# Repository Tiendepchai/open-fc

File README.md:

# open-fc (OPEN-FC MINIMAL v1.0 — Carrier PCB Rev K)

> **Status:** `HARDWARE DESIGN (REV K) & M0 VERIFICATION — BENCH ONLY` (Not flight-certified).

Custom minimal flight-controller carrier & companion stack built around a `WeAct STM32F405RGT6` running `ArduCopter / ChibiOS` (`OPENFCF405`) as the single flight-critical authority, paired with `ESP32 DevKit` (MAVLink2 Wi-Fi telemetry bridge) and `ESP32-CAM` (`OV2640` vision precision landing).

## Baseline Summary (Rev K — 100% THT)

- **Carrier PCB (`design`):** `60 × 68 mm` (`Rev K.1`, ADR-003), 2-layer FR4, 4× M3 mounting holes (`45 × 45 mm`), 100% THT (`23` discrete + `12` headers/sockets = `35` electrical parts + `4` M3 holes). Open-sky `U1` (`33.22×41.60 mm`), `U2` (`25.10×14.88 mm`), `U3` (`15.38×11.50 mm`); low-profile discretes (`≤ 5.5 mm`) nested under `U1`.
- **VBAT Sense (`design`):** Passive current-limited divider `220 kΩ (1%) / 18 kΩ (1%)` + `4.7 kΩ` series + `100 nF` into `PA0` (`TMUX1511PW` removed). `JP_C` (`PC0` current sense) stays **OPEN** by default.
- **Power Option 1 — Pixhawk Style (`confirmed`):** External UBEC `5V/3A` off ESC `BAT+ / BAT-` into `J_PWR (JST-XH 2P)`, star-routed into `+5V_COMP` (`J_WIFI`, `J_CAM`, `C1/C2 470 µF`) and `+5V_FC` via Schottky `D1 1N5822` (`U1`, `J_GPS`, `J_RC`, `C6 100 nF`).
- **Sensors & Peripherals (`measured` / `design`):** `MPU6500` + `BMP280` on `SPI1` (internal `~9 kΩ` CS pull-ups measured; external CS pull-ups removed), `BN-880` on `USART6` + `I2C2` (`18 kΩ` measured on module; PCB adds `R9/R10 4.7 kΩ` to `+3V3`), `MC7RE` SBUS on `UART4` via external inverted SBUS carrier PCB + `R12 (4.7 kΩ)` series protection (ADR-003).
- **Connectors (`confirmed`):** Standardized vertical THT `JST-XH 2.50 mm` (`2P, 3P, 4P×2, 6P, 8P`), `Pin 1 = +V`, `Pin 2 = GND` on all power-carrying ports.

## Roadmap Status

| Milestone | Scope | Status |
|---|---|---|
| **M0 — Hardware Verification** | Cold checks done (`PA9`, `NCS/CSB`, `BN-880 I2C`, pad orders); WeAct F405 V11 `8 MHz` HSE + `2×15` pinmap `1..30` + `ΔX = 27.94 mm` locked from vendor docs. Pending: 1:1 A4 paper fit check, `JST-XH` cable wiring polarity, `MC7RE` SBUS waveform, UBEC `5V/3A` dual-ESP32 load test. | **In Progress** |
| **M1 — PCB Rev K & FC Port** | **FW (`PASS`):** `OPENFCF405` (`Copter-4.6.3`, `HSE 8 MHz`) builds at `735,816 / 983,040 B` (`247 KB` headroom) with `SHARED_DMA_MASK=0` (`TIM4_UP` DMAR dedicated). **Schematic (`PASS`):** 4-sheet KiCad 10 Rev K.1 (`U1_P1/U1_P2` `verified_from_vendor_doc`, external SBUS carrier + `R12 4.7 kΩ`, `0` ERC violations, BOM sync `PASS` `23` discrete + `12` headers/connectors). **PCB (`PASS` / `design`):** `60 × 68 mm` 2-layer layout (`B.Cu` GND plane, `308` tracks, `67` vias, `45 × 45 mm` M3, `25.40 mm` WeAct inner-to-inner, open-sky `MPU6500`/`BMP280`/`WeAct` with 1:1 `F.Fab` outlines, low-profile discretes under `U1`), **`0` DRC errors/warnings/unconnected/parity**; **1:1 A4 PDF** at `hardware/fabrication/open-fc-carrier-rev-k-1to1-A4.pdf` (physical fit check pending). | **In Progress (FW + Sch + PCB DRC=0 PASS; Fit Check Pending)** |
| **M2 — Carrier Bring-up & Gateway** | Staged PCB solder (`PA0` check pre-MCU), ArduCopter bench bring-up (props off), `esp32-wifi` MAVLink2 UDP↔UART1 bridge. | Planned |
| **M3 — Vision Pipeline** | `OV2640` calibration, `esp32-cam` marker detection → MAVLink2 `LANDING_TARGET`, FPS/latency benchmark. | Planned |
| **M4 — SITL & Bench Integration** | ArduCopter SITL + vision replay; F450 prop-off bench fault-injection tests. | Planned |
| **M5 — Flight Release** | IMU damping, BMP280 wind foam, measured `BATT_VOLT_MULT`, `docs/safety-case.md` approval. | **BLOCKED** |

## Repository Map

- `AGENTS.md` — mandatory engineering guardrails and safety rules.
- `docs/` — master baseline (`OPEN_FC_MINIMAL_v1.0.md`), verified pinmap, Rev K BOM, ADRs, verification logs, safety case.
- `hardware/` — KiCad Rev K project, reference schematics, fabrication outputs, mechanical mounts.
- `firmware/` — pinned `ardupilot/` submodule, custom `board-openfcf405/`, `esp32-wifi/`, `esp32-cam/`.
- `sim/` — SITL launch configs, vision replay datasets, fault-injection scenarios.
- `scripts/` — FC build + 1 MB Flash check (`build-fc.sh`), ChibiOS DMA analyzer (`check-dma.py`), BOM sync check (`check-bom-sync.py`).
- `reports/` — dated build logs, ERC/DRC reports, bench verification outputs.

## Quick Commands (M1–M4 Software Verification)

```bash
# 1. Verify BOM CSV consistency (and cross-check KiCad export when available)
python3 scripts/check-bom-sync.py

# 2. Build OPENFCF405 bootloader + ArduCopter (verifies < 1 MB Flash, TIM4 DMA, 11 ELF safety symbols)
./scripts/build-fc.sh

# 3. Verify companion C11 modules (esp32-wifi, esp32-cam), vision replay, and M4 fault-injection suite
./scripts/test-companions.sh

# 4. Run KiCad 10 ERC=0, DRC=0 + schematic parity, 1:1 A4 PDF export, and BOM sync (once PCB exists)
./scripts/verify-kicad.sh
```

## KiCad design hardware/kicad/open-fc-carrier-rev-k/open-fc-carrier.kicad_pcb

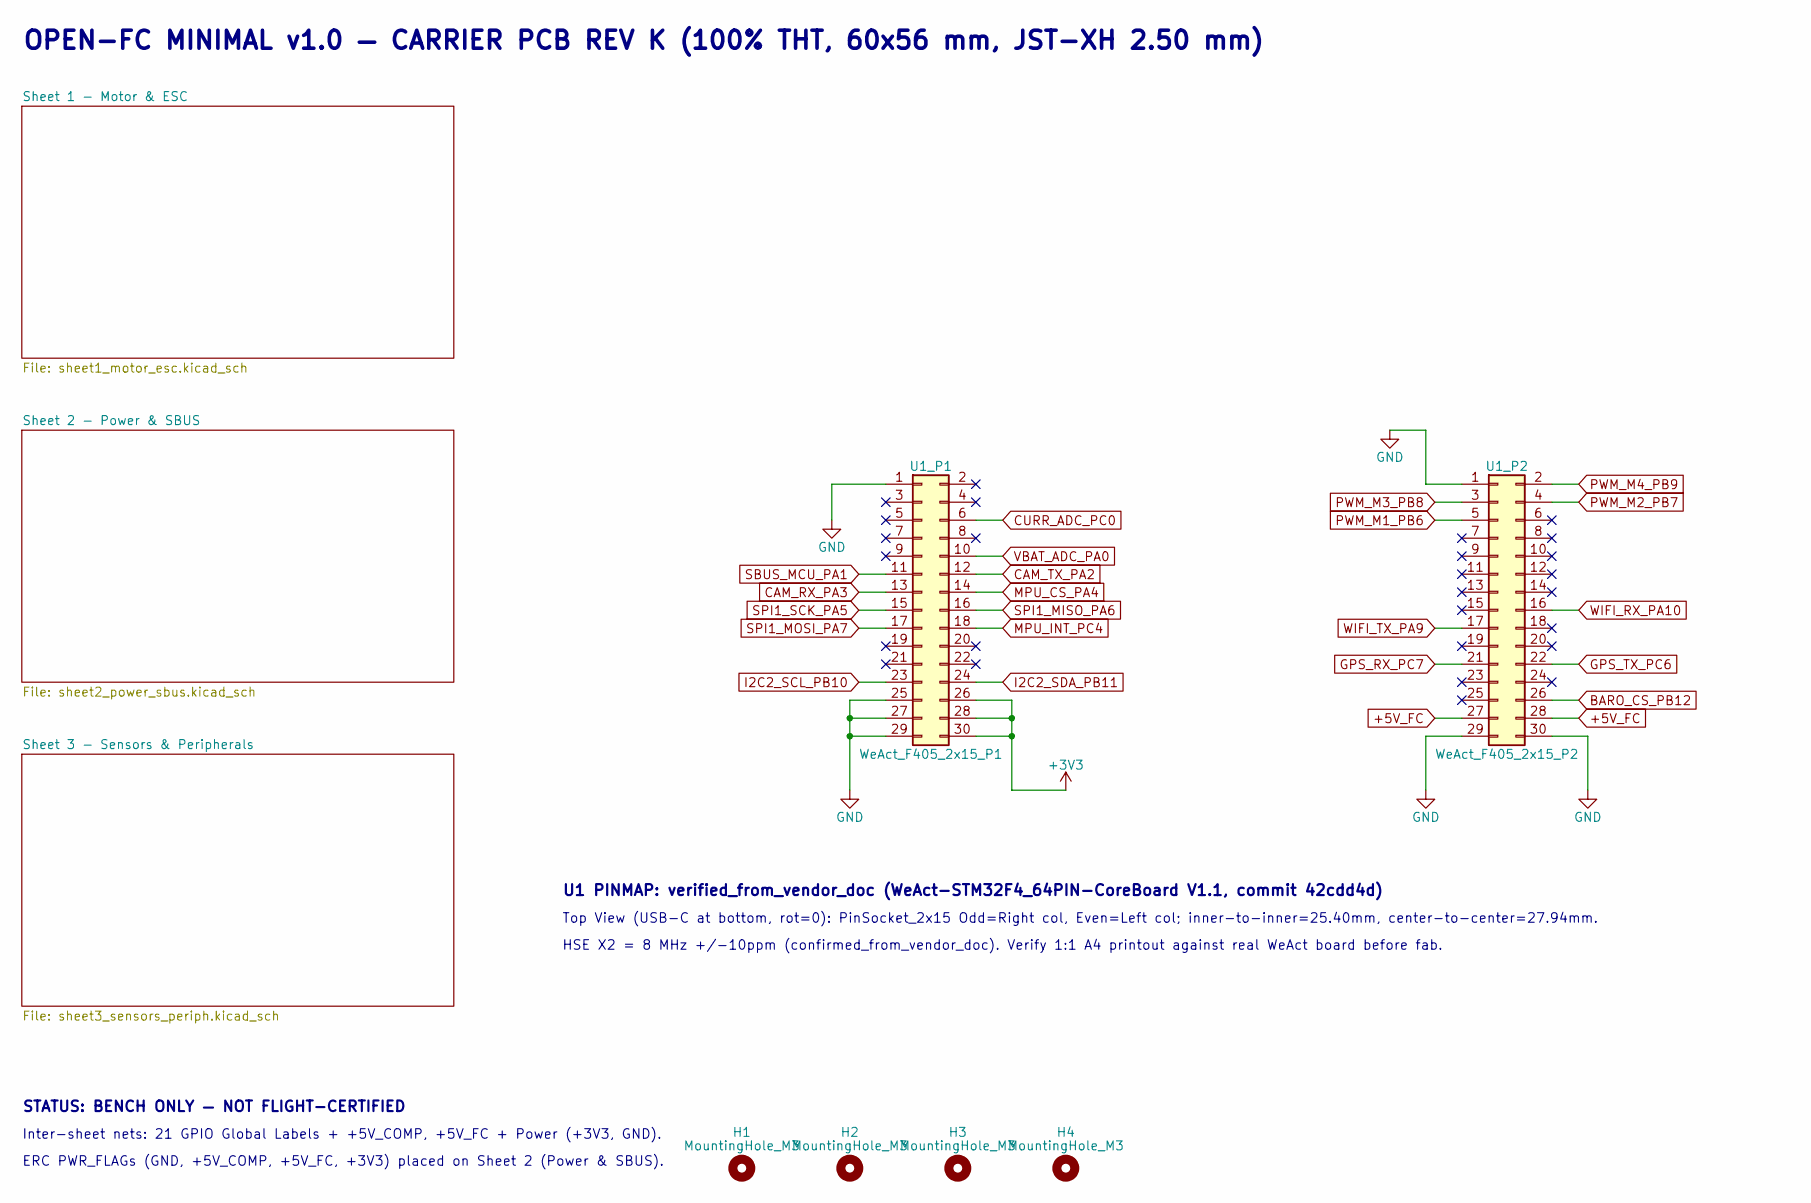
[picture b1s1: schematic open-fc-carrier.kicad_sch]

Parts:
H1, H2, H3, H4: MountingHole_M3; MountingHole_3.2mm_M3
U1_P1: WeAct_F405_2x15_P1; PinSocket_2x15_P2.54mm_Vertical
U1_P2: WeAct_F405_2x15_P2; PinSocket_2x15_P2.54mm_Vertical

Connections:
+3V3: U1_P1.26, U1_P1.28, U1_P1.30; also elsewhere on the board
+5V_FC: U1_P2.27, U1_P2.28; also elsewhere on the board
BARO_CS_PB12: U1_P2.26; also elsewhere on the board
CAM_RX_PA3: U1_P1.13; also elsewhere on the board
CAM_TX_PA2: U1_P1.12; also elsewhere on the board
CURR_ADC_PC0: U1_P1.6; also elsewhere on the board
GND: U1_P1.1, U1_P1.25, U1_P1.27, U1_P1.29, U1_P2.1, U1_P2.29, U1_P2.30; also elsewhere on the board
GPS_RX_PC7: U1_P2.21; also elsewhere on the board
GPS_TX_PC6: U1_P2.22; also elsewhere on the board
I2C2_SCL_PB10: U1_P1.23; also elsewhere on the board
I2C2_SDA_PB11: U1_P1.24; also elsewhere on the board
MPU_CS_PA4: U1_P1.14; also elsewhere on the board
MPU_INT_PC4: U1_P1.18; also elsewhere on the board
PWM_M1_PB6: U1_P2.5; also elsewhere on the board
PWM_M2_PB7: U1_P2.4; also elsewhere on the board
PWM_M3_PB8: U1_P2.3; also elsewhere on the board
PWM_M4_PB9: U1_P2.2; also elsewhere on the board
SBUS_MCU_PA1: U1_P1.11; also elsewhere on the board
SPI1_MISO_PA6: U1_P1.16; also elsewhere on the board
SPI1_MOSI_PA7: U1_P1.17; also elsewhere on the board
SPI1_SCK_PA5: U1_P1.15; also elsewhere on the board
VBAT_ADC_PA0: U1_P1.10; also elsewhere on the board
WIFI_RX_PA10: U1_P2.16; also elsewhere on the board
WIFI_TX_PA9: U1_P2.17; also elsewhere on the board

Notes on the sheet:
OPEN-FC MINIMAL v1.0 — CARRIER PCB REV K (100% THT, 60x56 mm, JST-XH 2.50 mm)
STATUS: BENCH ONLY — NOT FLIGHT-CERTIFIED
Inter-sheet nets: 21 GPIO Global Labels + +5V_COMP, +5V_FC + Power (+3V3, GND).
ERC PWR_FLAGs (GND, +5V_COMP, +5V_FC, +3V3) placed on Sheet 2 (Power & SBUS).
U1 PINMAP: verified_from_vendor_doc (WeAct-STM32F4_64PIN-CoreBoard V1.1, commit 42cdd4d)
Top View (USB-C at bottom, rot=0): PinSocket_2x15 Odd=Right col, Even=Left col; inner-to-inner=25.40mm, center-to-center=27.94mm.
HSE X2 = 8 MHz +/-10ppm (confirmed_from_vendor_doc). Verify 1:1 A4 printout against real WeAct board before fab.

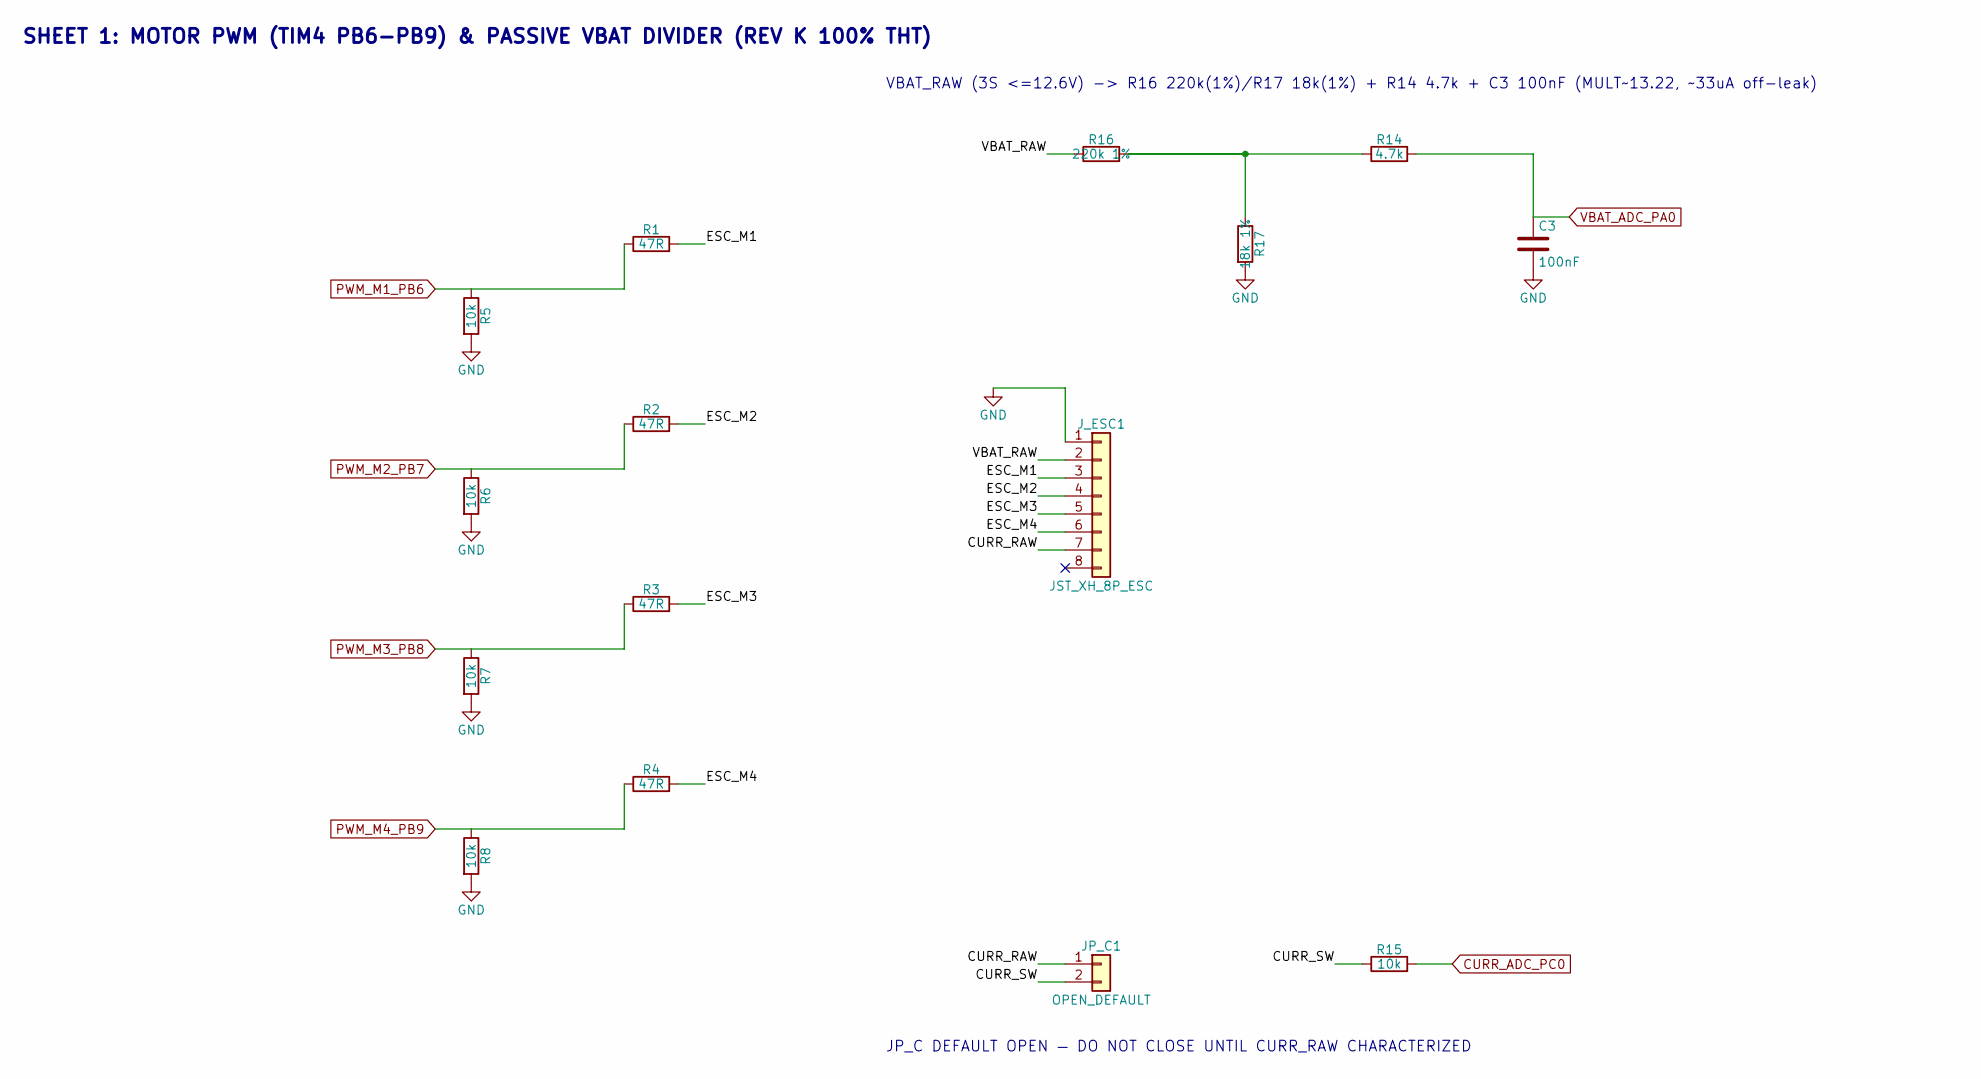
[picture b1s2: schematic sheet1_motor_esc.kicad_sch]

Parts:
C3: 100nF; C_Disc_D5.0mm_W2.5mm_P5.00mm
JP_C1: OPEN_DEFAULT; PinHeader_1x02_P2.54mm_Vertical
J_ESC1: JST_XH_8P_ESC; JST_XH_B8B-XH-A_1x08_P2.50mm_Vertical
R1, R2, R3, R4: 47R; R_Axial_DIN0207_L6.3mm_D2.5mm_P7.62mm_Horizontal
R5, R6, R7, R8, R15: 10k; R_Axial_DIN0207_L6.3mm_D2.5mm_P7.62mm_Horizontal
R14: 4.7k; R_Axial_DIN0207_L6.3mm_D2.5mm_P7.62mm_Horizontal
R16: 220k 1%; R_Axial_DIN0207_L6.3mm_D2.5mm_P7.62mm_Horizontal
R17: 18k 1%; R_Axial_DIN0207_L6.3mm_D2.5mm_P7.62mm_Horizontal

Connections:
/Sheet 1 - Motor & ESC/CURR_RAW: JP_C1.1, J_ESC1.7
/Sheet 1 - Motor & ESC/CURR_SW: JP_C1.2, R15.1
/Sheet 1 - Motor & ESC/ESC_M1: J_ESC1.3, R1.2
/Sheet 1 - Motor & ESC/ESC_M2: J_ESC1.4, R2.2
/Sheet 1 - Motor & ESC/ESC_M3: J_ESC1.5, R3.2
/Sheet 1 - Motor & ESC/ESC_M4: J_ESC1.6, R4.2
/Sheet 1 - Motor & ESC/VBAT_RAW: J_ESC1.2, R16.1
CURR_ADC_PC0: R15.2; also elsewhere on the board
GND: C3.2, J_ESC1.1, R5.2, R6.2, R7.2, R8.2, R17.2; also elsewhere on the board
unnamed: R14.1, R16.2, R17.1
PWM_M1_PB6: R1.1, R5.1; also elsewhere on the board
PWM_M2_PB7: R2.1, R6.1; also elsewhere on the board
PWM_M3_PB8: R3.1, R7.1; also elsewhere on the board
PWM_M4_PB9: R4.1, R8.1; also elsewhere on the board
VBAT_ADC_PA0: C3.1, R14.2; also elsewhere on the board

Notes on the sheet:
SHEET 1: MOTOR PWM (TIM4 PB6-PB9) & PASSIVE VBAT DIVIDER (REV K 100% THT)
VBAT_RAW (3S <=12.6V) -> R16 220k(1%)/R17 18k(1%) + R14 4.7k + C3 100nF (MULT~13.22, ~33uA off-leak)
JP_C DEFAULT OPEN — DO NOT CLOSE UNTIL CURR_RAW CHARACTERIZED

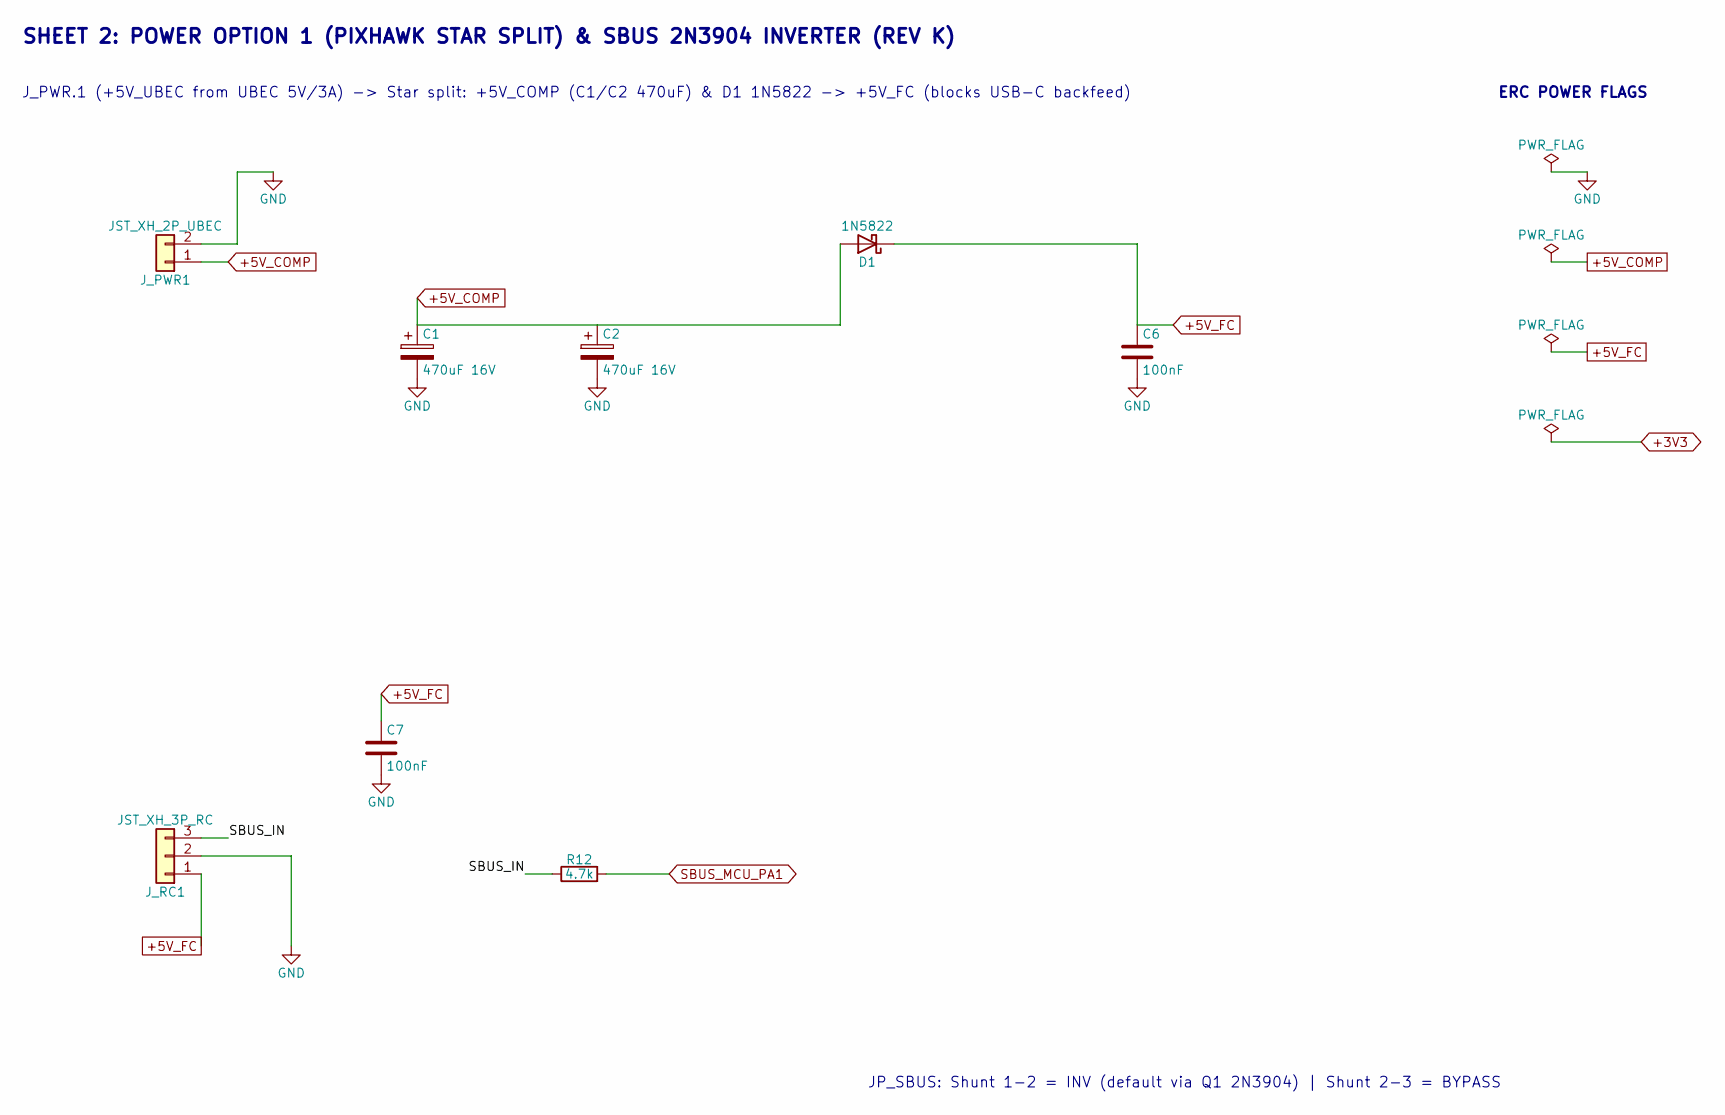
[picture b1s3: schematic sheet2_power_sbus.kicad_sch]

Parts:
C1, C2: 470uF 16V; CP_Radial_D8.0mm_P3.50mm
C6, C7: 100nF; C_Disc_D5.0mm_W2.5mm_P5.00mm
D1: 1N5822; D_DO-201AD_P12.70mm_Horizontal
J_PWR1: JST_XH_2P_UBEC; JST_XH_B2B-XH-A_1x02_P2.50mm_Vertical
J_RC1: JST_XH_3P_RC; JST_XH_B3B-XH-A_1x03_P2.50mm_Vertical
R12: 4.7k; R_Axial_DIN0207_L6.3mm_D2.5mm_P7.62mm_Horizontal

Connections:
+5V_COMP: C1.1, C2.1, D1.2 (A), J_PWR1.1; also elsewhere on the board
+5V_FC: C6.1, C7.1, D1.1 (K), J_RC1.1; also elsewhere on the board
/Sheet 2 - Power & SBUS/SBUS_IN: J_RC1.3, R12.1
GND: C1.2, C2.2, C6.2, C7.2, J_PWR1.2, J_RC1.2; also elsewhere on the board
SBUS_MCU_PA1: R12.2; also elsewhere on the board

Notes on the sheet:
SHEET 2: POWER OPTION 1 (PIXHAWK STAR SPLIT) & SBUS 2N3904 INVERTER (REV K)
J_PWR.1 (+5V_UBEC from UBEC 5V/3A) -> Star split: +5V_COMP (C1/C2 470uF) & D1 1N5822 -> +5V_FC (blocks USB-C backfeed)
JP_SBUS: Shunt 1-2 = INV (default via Q1 2N3904) | Shunt 2-3 = BYPASS
ERC POWER FLAGS

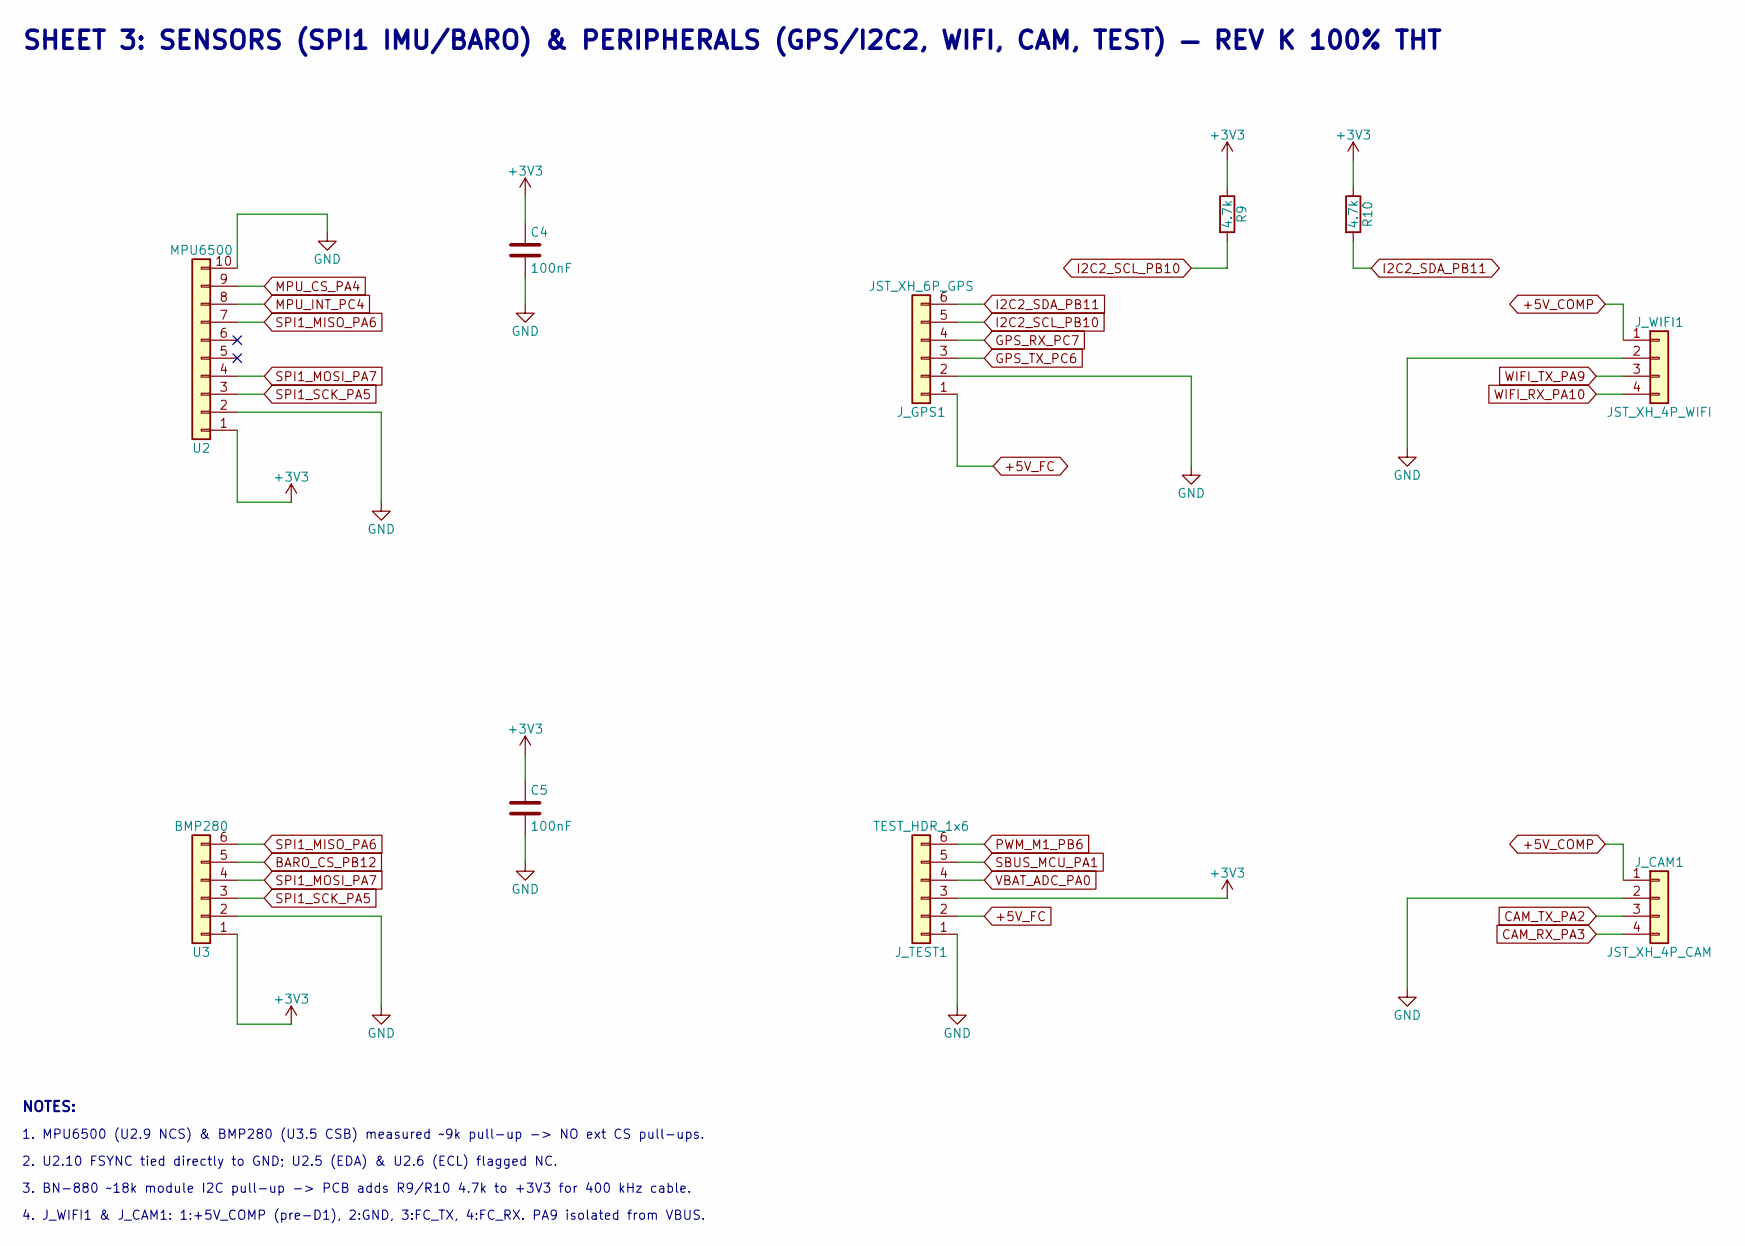
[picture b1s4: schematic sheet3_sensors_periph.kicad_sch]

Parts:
C4, C5: 100nF; C_Disc_D5.0mm_W2.5mm_P5.00mm
J_CAM1: JST_XH_4P_CAM; JST_XH_B4B-XH-A_1x04_P2.50mm_Vertical
J_GPS1: JST_XH_6P_GPS; JST_XH_B6B-XH-A_1x06_P2.50mm_Vertical
J_TEST1: TEST_HDR_1x6; PinHeader_1x06_P2.54mm_Vertical
J_WIFI1: JST_XH_4P_WIFI; JST_XH_B4B-XH-A_1x04_P2.50mm_Vertical
R9, R10: 4.7k; R_Axial_DIN0207_L6.3mm_D2.5mm_P7.62mm_Horizontal
U2: MPU6500; PinSocket_1x10_P2.54mm_Vertical
U3: BMP280; PinSocket_1x06_P2.54mm_Vertical

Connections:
+3V3: C4.1, C5.1, J_TEST1.3, R9.1, R10.1, U2.1, U3.1; also elsewhere on the board
+5V_COMP: J_CAM1.1, J_WIFI1.1; also elsewhere on the board
+5V_FC: J_GPS1.1, J_TEST1.2; also elsewhere on the board
BARO_CS_PB12: U3.5; also elsewhere on the board
CAM_RX_PA3: J_CAM1.4; also elsewhere on the board
CAM_TX_PA2: J_CAM1.3; also elsewhere on the board
GND: C4.2, C5.2, J_CAM1.2, J_GPS1.2, J_TEST1.1, J_WIFI1.2, U2.2, U2.10, U3.2; also elsewhere on the board
GPS_RX_PC7: J_GPS1.4; also elsewhere on the board
GPS_TX_PC6: J_GPS1.3; also elsewhere on the board
I2C2_SCL_PB10: J_GPS1.5, R9.2; also elsewhere on the board
I2C2_SDA_PB11: J_GPS1.6, R10.2; also elsewhere on the board
MPU_CS_PA4: U2.9; also elsewhere on the board
MPU_INT_PC4: U2.8; also elsewhere on the board
PWM_M1_PB6: J_TEST1.6; also elsewhere on the board
SBUS_MCU_PA1: J_TEST1.5; also elsewhere on the board
SPI1_MISO_PA6: U2.7, U3.6; also elsewhere on the board
SPI1_MOSI_PA7: U2.4, U3.4; also elsewhere on the board
SPI1_SCK_PA5: U2.3, U3.3; also elsewhere on the board
VBAT_ADC_PA0: J_TEST1.4; also elsewhere on the board
WIFI_RX_PA10: J_WIFI1.4; also elsewhere on the board
WIFI_TX_PA9: J_WIFI1.3; also elsewhere on the board

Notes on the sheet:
SHEET 3: SENSORS (SPI1 IMU/BARO) & PERIPHERALS (GPS/I2C2, WIFI, CAM, TEST) — REV K 100% THT
NOTES:
1. MPU6500 (U2.9 NCS) & BMP280 (U3.5 CSB) measured ~9k pull-up -> NO ext CS pull-ups.
2. U2.10 FSYNC tied directly to GND; U2.5 (EDA) & U2.6 (ECL) flagged NC.
3. BN-880 ~18k module I2C pull-up -> PCB adds R9/R10 4.7k to +3V3 for 400 kHz cable.
4. J_WIFI1 & J_CAM1: 1:+5V_COMP (pre-D1), 2:GND, 3:FC_TX, 4:FC_RX. PA9 isolated from VBUS.

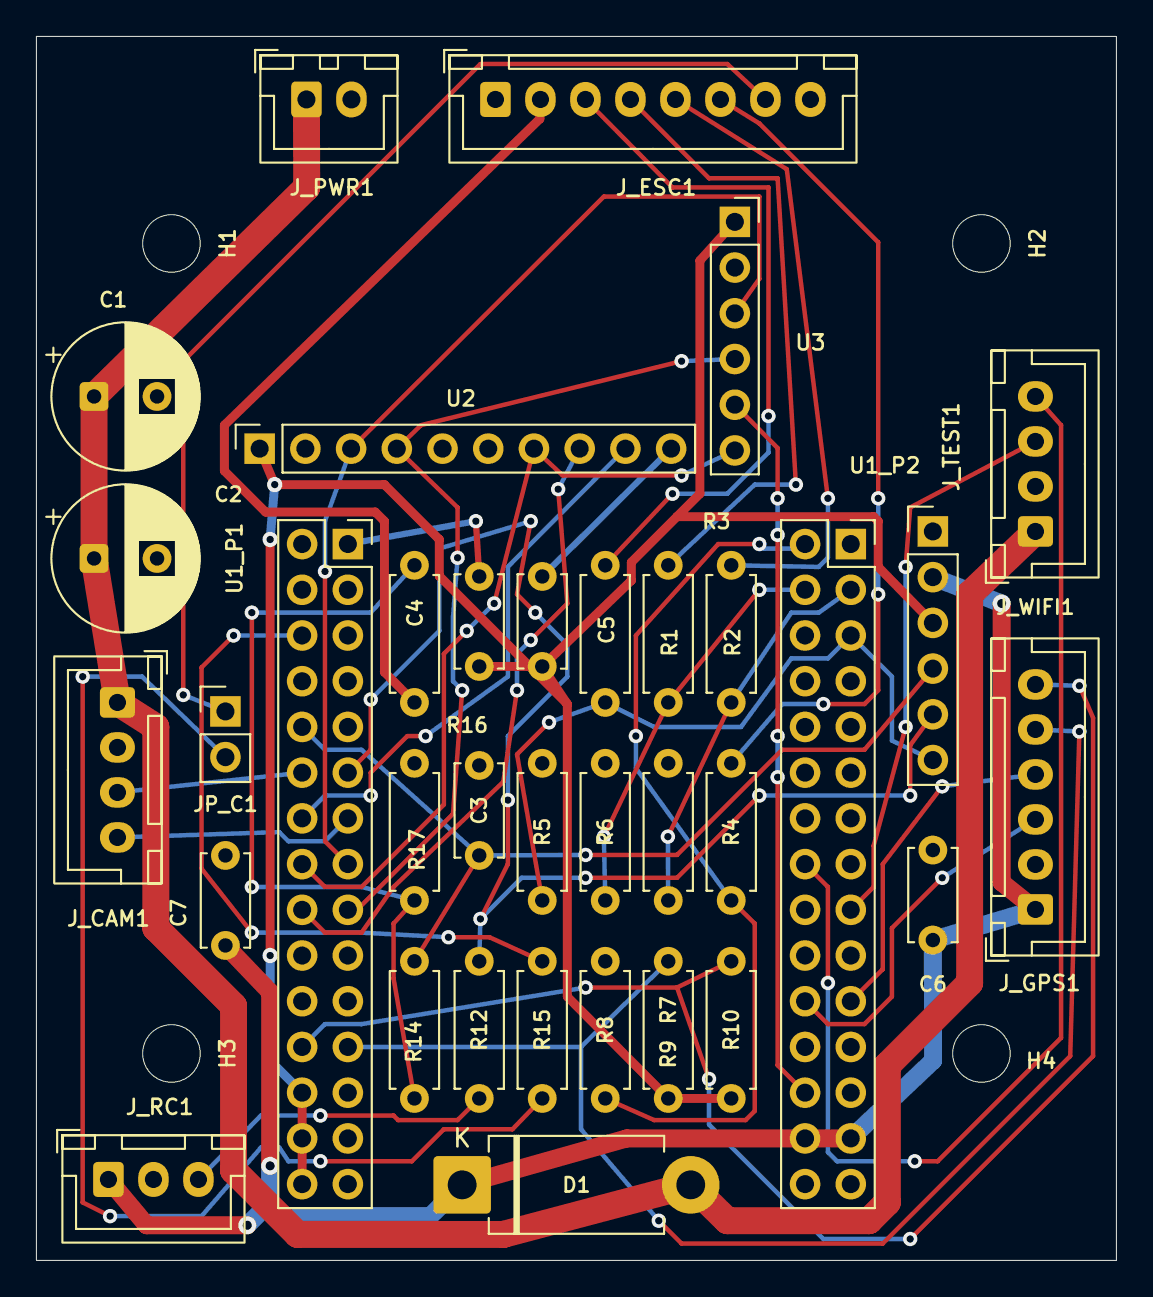
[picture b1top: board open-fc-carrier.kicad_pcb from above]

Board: 2 copper layers, 60.0 x 68.0 mm, 39 parts (0 on the bottom side), 34 nets.

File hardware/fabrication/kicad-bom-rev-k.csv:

"Refs","Value","Footprint","Qty","DNP"
"C1","470uF 16V","Capacitor_THT:CP_Radial_D8.0mm_P3.50mm","1",""
"C2","470uF 16V","Capacitor_THT:CP_Radial_D8.0mm_P3.50mm","1",""
"C3","100nF","Capacitor_THT:C_Disc_D5.0mm_W2.5mm_P5.00mm","1",""
"C4","100nF","Capacitor_THT:C_Disc_D5.0mm_W2.5mm_P5.00mm","1",""
"C5","100nF","Capacitor_THT:C_Disc_D5.0mm_W2.5mm_P5.00mm","1",""
"C6","100nF","Capacitor_THT:C_Disc_D5.0mm_W2.5mm_P5.00mm","1",""
"C7","100nF","Capacitor_THT:C_Disc_D5.0mm_W2.5mm_P5.00mm","1",""
"D1","1N5822","Diode_THT:D_DO-201AD_P12.70mm_Horizontal","1",""
"H1","MountingHole_M3","MountingHole:MountingHole_3.2mm_M3","1",""
"H2","MountingHole_M3","MountingHole:MountingHole_3.2mm_M3","1",""
"H3","MountingHole_M3","MountingHole:MountingHole_3.2mm_M3","1",""
"H4","MountingHole_M3","MountingHole:MountingHole_3.2mm_M3","1",""
"JP_C1","OPEN_DEFAULT","Connector_PinHeader_2.54mm:PinHeader_1x02_P2.54mm_Vertical","1",""
"J_CAM1","JST_XH_4P_CAM","Connector_JST:JST_XH_B4B-XH-A_1x04_P2.50mm_Vertical","1",""
"J_ESC1","JST_XH_8P_ESC","Connector_JST:JST_XH_B8B-XH-A_1x08_P2.50mm_Vertical","1",""
"J_GPS1","JST_XH_6P_GPS","Connector_JST:JST_XH_B6B-XH-A_1x06_P2.50mm_Vertical","1",""
"J_PWR1","JST_XH_2P_UBEC","Connector_JST:JST_XH_B2B-XH-A_1x02_P2.50mm_Vertical","1",""
"J_RC1","JST_XH_3P_RC","Connector_JST:JST_XH_B3B-XH-A_1x03_P2.50mm_Vertical","1",""
"J_TEST1","TEST_HDR_1x6","Connector_PinHeader_2.54mm:PinHeader_1x06_P2.54mm_Vertical","1",""
"J_WIFI1","JST_XH_4P_WIFI","Connector_JST:JST_XH_B4B-XH-A_1x04_P2.50mm_Vertical","1",""
"R1","47R","Resistor_THT:R_Axial_DIN0207_L6.3mm_D2.5mm_P7.62mm_Horizontal","1",""
"R2","47R","Resistor_THT:R_Axial_DIN0207_L6.3mm_D2.5mm_P7.62mm_Horizontal","1",""
"R3","47R","Resistor_THT:R_Axial_DIN0207_L6.3mm_D2.5mm_P7.62mm_Horizontal","1",""
"R4","47R","Resistor_THT:R_Axial_DIN0207_L6.3mm_D2.5mm_P7.62mm_Horizontal","1",""
"R5","10k","Resistor_THT:R_Axial_DIN0207_L6.3mm_D2.5mm_P7.62mm_Horizontal","1",""
"R6","10k","Resistor_THT:R_Axial_DIN0207_L6.3mm_D2.5mm_P7.62mm_Horizontal","1",""
"R7","10k","Resistor_THT:R_Axial_DIN0207_L6.3mm_D2.5mm_P7.62mm_Horizontal","1",""
"R8","10k","Resistor_THT:R_Axial_DIN0207_L6.3mm_D2.5mm_P7.62mm_Horizontal","1",""
"R9","4.7k","Resistor_THT:R_Axial_DIN0207_L6.3mm_D2.5mm_P7.62mm_Horizontal","1",""
"R10","4.7k","Resistor_THT:R_Axial_DIN0207_L6.3mm_D2.5mm_P7.62mm_Horizontal","1",""
"R12","4.7k","Resistor_THT:R_Axial_DIN0207_L6.3mm_D2.5mm_P7.62mm_Horizontal","1",""
"R14","4.7k","Resistor_THT:R_Axial_DIN0207_L6.3mm_D2.5mm_P7.62mm_Horizontal","1",""
"R15","10k","Resistor_THT:R_Axial_DIN0207_L6.3mm_D2.5mm_P7.62mm_Horizontal","1",""
"R16","220k 1%","Resistor_THT:R_Axial_DIN0207_L6.3mm_D2.5mm_P7.62mm_Horizontal","1",""
"R17","18k 1%","Resistor_THT:R_Axial_DIN0207_L6.3mm_D2.5mm_P7.62mm_Horizontal","1",""
"U1_P1","WeAct_F405_2x15_P1","Connector_PinSocket_2.54mm:PinSocket_2x15_P2.54mm_Vertical","1",""
"U1_P2","WeAct_F405_2x15_P2","Connector_PinSocket_2.54mm:PinSocket_2x15_P2.54mm_Vertical","1",""
"U2","MPU6500","Connector_PinSocket_2.54mm:PinSocket_1x10_P2.54mm_Vertical","1",""
"U3","BMP280","Connector_PinSocket_2.54mm:PinSocket_1x06_P2.54mm_Vertical","1",""
